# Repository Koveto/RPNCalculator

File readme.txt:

Reverse Polish Notation (RPN) Calculator

Contributors:
Kale Erickson
Kobe Goodwin
Gabe Wichmann

NDSU Senior Design project
ECE 403/405
Fall 2024 - Spring 2025
OneNote: https://ndusbpos-my.sharepoint.com/:o:/g/personal/kale_erickson_ndus_edu/EvFGwJnf-eBBiN7WtRWUvscBkYgOqBa3zW2gMm88qsdTBQ?e=oOiAU5

Project Description

HP-42S is a reverse polish notation (RPN) calculator championed by 
engineers around the world. RPN calculators sell for $400 and higher:
a forbidding price for college students. Our committee will design an
alternative HP-42S calculator that is affordable and reliable. Our 
RPN calculator solution will operate on mobile hardware powered by a
battery and disconnected from external devices. Our committee aims to
construct a RPN calculator engineering students could feasibly use on
exams. 

Instructions

1. Hold the button on the Raspberry Pi Pico
2. Plug the Pico into the computer
3. Drag "rp2-pico-micropython-doubleprecision-1-19.uf2" into the new directory
4. Unplug the Pico
5. Release the button
6. Plug the Pico into the computer
7. Use Thonny to save files in "program" to Pico

About the LCD

The program includes lcd.py and lcd_i2c.py.
lcd.py:
   communicates to the 20x4 LCD (using parallel interface)
lcd_i2c.py:
   NOT NECESSARY TO DOWNLOAD.
   used by an old PCB revision to communicate to its 16x2 LCD
   (using I2C protocol). 
To switch from one to the other,
   remove commented-out LCD_I2C import/initialization in main.py.
   comment out LCD import/initialization in main.py. 
Different LCD?
   the program only supports 20x4 parallel or 16x2 I2C.
   change ROWS and COLUMNS in lcd.py or lcd_i2c.py.
   revise lcd.write_to(...) commands in main.py and calculator.py.

Program your own game!

lcd.py is necessary.
Revise button_labels.py with your buttons and mapping.
Revise push_buttons.py if necessary.
Create your own main.py to read input and display output.

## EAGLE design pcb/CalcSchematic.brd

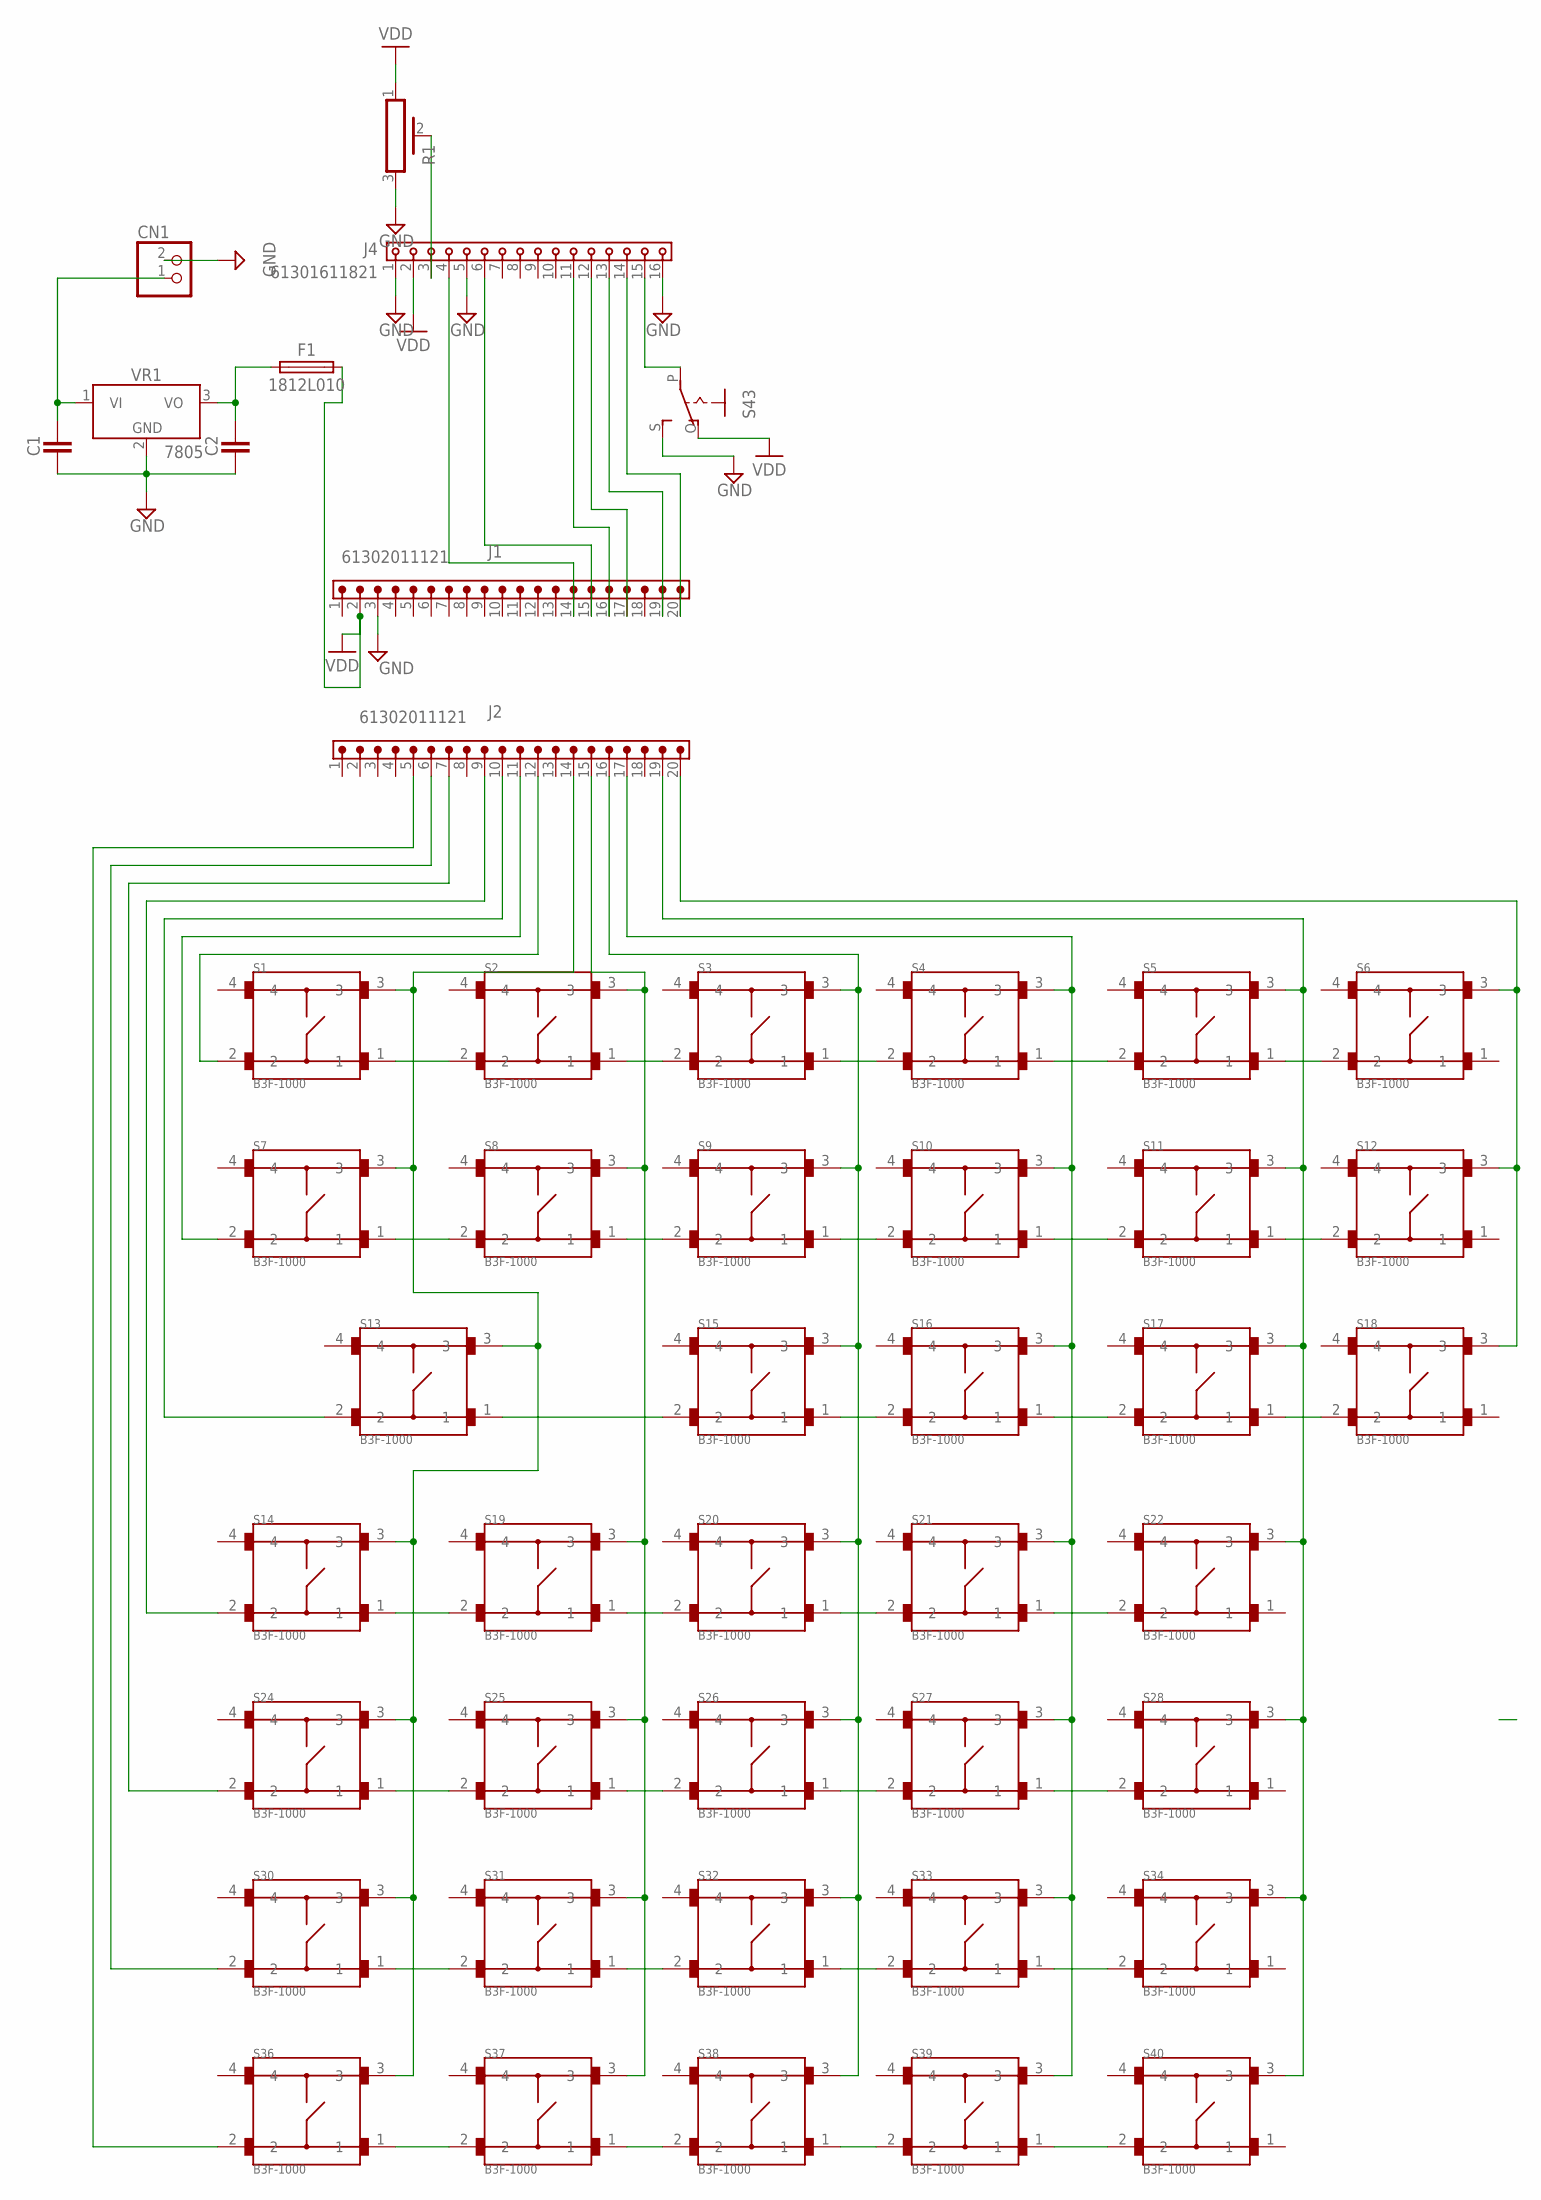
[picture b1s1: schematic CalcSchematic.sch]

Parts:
C1, C2: CAPACITOR_CHIP-1206(3216-METRIC); CAPC3216X135
CN1: JST_2PIN-THM; JST-PH-2-THM
F1: 1812L010; FUSC4532X125
J1, J2: 61302011121
J4: 61301611821
R1: POT_PV36P; PV36P
S1, S2, S3, S4, S5, S6, S7, S8, S9, S10, S11, S12, S13, S14, S15, S16, S17, S18, S19, S20, S21, S22, S24, S25, S26, S27, S28, S30, S31, S32, S33, S34, S36, S37, S38, S39, S40: B3F-1000; SW_B3F-1000
S43: EG1218S; EG1218
VR1: 7805; TO220V

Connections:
GND: C1.2, C2.2, CN1.2 (1), J1.3, J4.1, J4.5, J4.16, R1.3, S43.S, VR1.2 (GND)
unnamed: S1.1, S2.2
unnamed: S2.1, S3.2
unnamed: S3.1, S4.2
unnamed: S4.1, S5.2
unnamed: S5.1, S6.2
unnamed: S7.1, S8.2
unnamed: S8.1, S9.2
unnamed: S9.1, S10.2
unnamed: S10.1, S11.2
unnamed: S11.1, S12.2
unnamed: S13.1, S15.2
unnamed: S15.1, S16.2
unnamed: S16.1, S17.2
unnamed: S17.1, S18.2
unnamed: S14.1, S19.2
unnamed: S19.1, S20.2
unnamed: S20.1, S21.2
unnamed: S21.1, S22.2
unnamed: S24.1, S25.2
unnamed: S25.1, S26.2
unnamed: S26.1, S27.2
unnamed: S27.1, S28.2
unnamed: C2.1, F1.1, VR1.3 (VO)
unnamed: S30.1, S31.2
unnamed: S31.1, S32.2
unnamed: S32.1, S33.2
unnamed: S33.1, S34.2
unnamed: S36.1, S37.2
unnamed: S37.1, S38.2
unnamed: S38.1, S39.2
unnamed: S39.1, S40.2
unnamed: J2.14, S1.3, S7.3, S13.3, S14.3, S24.3, S30.3, S36.3
unnamed: J2.15, S2.3, S8.3, S19.3, S25.3, S31.3, S37.3
unnamed: J2.16, S3.3, S9.3, S15.3, S20.3, S26.3, S32.3, S38.3
unnamed: J2.17, S4.3, S10.3, S16.3, S21.3, S27.3, S33.3, S39.3
unnamed: J2.19, S5.3, S11.3, S17.3, S22.3, S28.3, S34.3, S40.3
unnamed: J2.20, S6.3, S12.3, S18.3
unnamed: J2.12, S1.2
unnamed: J2.11, S7.2
unnamed: J2.10, S13.2
unnamed: J2.9, S14.2
unnamed: J2.7, S24.2
unnamed: J2.6, S30.2
unnamed: J2.5, S36.2
unnamed: J4.3, R1.2
unnamed: J1.14, J4.4
unnamed: J1.15, J4.6
unnamed: J1.16, J4.11
unnamed: J1.17, J4.12
unnamed: J1.19, J4.13
unnamed: J1.20, J4.14
unnamed: J4.15, S43.P
unnamed: C1.1, CN1.1 (2), VR1.1 (VI)
VDD: F1.2, J1.2, J4.2, R1.1, S43.O

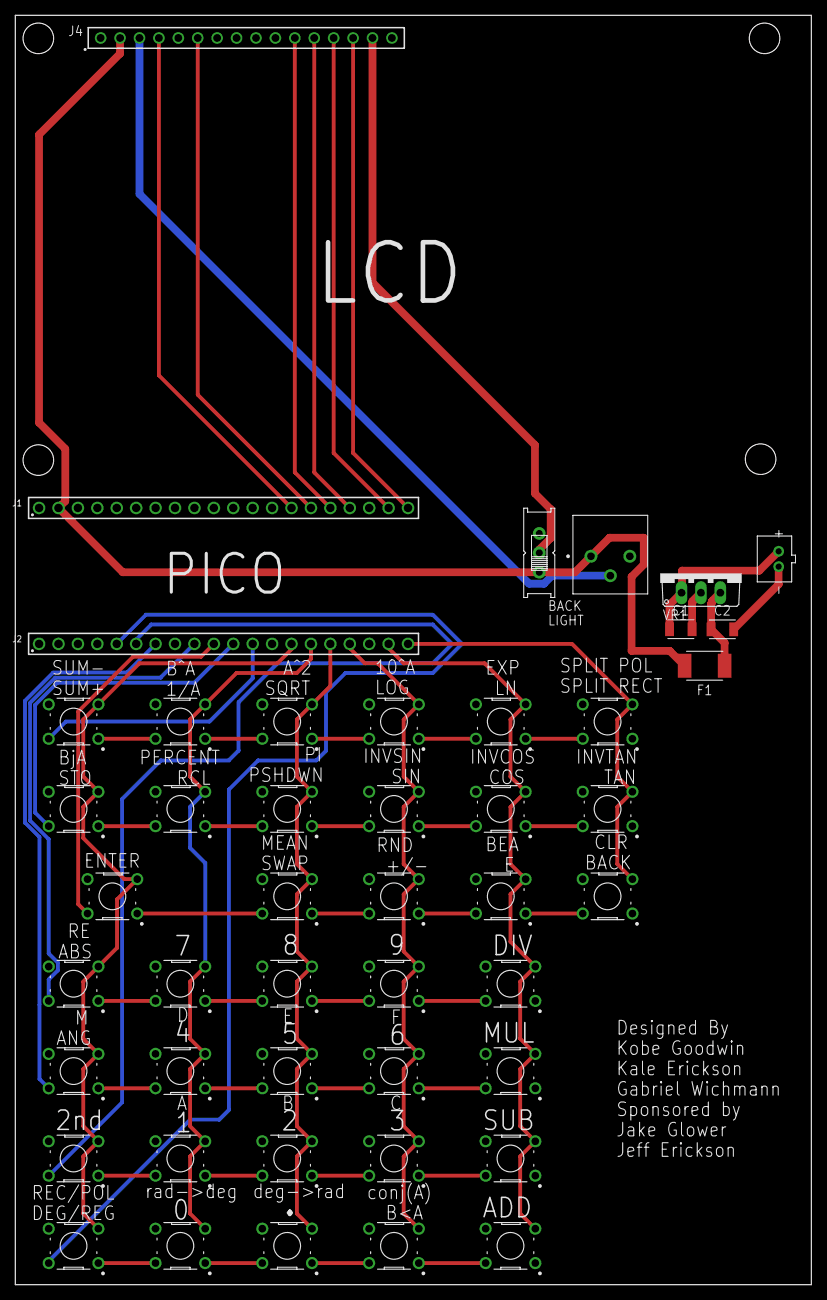
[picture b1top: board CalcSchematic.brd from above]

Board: 2 copper layers, 104.1 x 166.0 mm, 47 parts (0 on the bottom side), 55 nets.

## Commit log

2024-09-15 UI Button detection
2024-09-17 Numerical Input
2024-10-06 Arithmetic operations implemented. Divide By Zero displayed on top column when raised.
2024-10-06 Backspace/Enter methods resolved for numbers extending beyond DIGITS_ON_SCREEN
2024-10-06 Orange/Clear button
2024-10-06 Orange deactivates after use
2024-10-06 Fixed previous commit
2024-10-06 Division operands flipped
2024-10-06 Documented code. Simplified using peek() call.
2024-10-06 pushOperation flowchart
2024-10-06 appendZeros flowchart
2024-10-06 addition flowchart
2024-10-06 button35 flowchart
2024-10-06 button27 flowchart
2024-10-06 button22 flowchart
2024-10-06 button17 flowchart
2024-10-08 numberPressed flowchart
2024-10-08 Combined flowcharts pdf
2024-10-28 Pico button detection
2024-10-29 Keypad input detection
2024-10-29 Keypad + Button input
2024-10-29 Task 1 Functions to Pico
2024-10-29 Fourth button: Orange/Clear
2024-11-12 Decimal input
2024-11-12 One digit exponentiation
2024-11-12 Input "complex" numbers
2024-12-15 Push button inverter
2024-12-16 Complex/Exponential arithmetic
2024-12-20 connectLCD
2024-12-20 Button Array
2024-12-21 rpnCalculator I/O
2024-12-22 Addition/Subtraction
2024-12-23 Long Division
2024-12-24 Multiplication/Division
2024-12-27 Stack
2025-01-01 Real Whole Number Input
2025-02-11 I2C Connection
2025-02-11 Documented code and removed old breadboard programs
2025-02-11 Emptied display, removed old imports
2025-02-11 Progress on single precision solution
2025-02-13 Program revision
2025-02-13 Trig, Log, Negate, Reciprocal, Swap
2025-02-13 Morning's code
2025-02-14 Complex revisions in progress
2025-02-16 Main flowchart
2025-02-17 Push Button Flowchart
2025-02-24 Squish complex numbers
2025-03-03 Button Labels added
2025-03-03 Button Labels
2025-03-03 Parallel program drafted
2025-03-19 Four row display
2025-04-14 Free42 Sim
2025-04-23 Added modulus and gamma
2025-04-25 Started on adding hex
2025-04-28 Fixed orient bug. Add hex support
2025-05-04 Two minute video
2025-05-04 Cleaned up repo
2025-05-07 Condensed parallel LCD functions to lcd.py. Integrated old I2C code so program can run on old PCB
2025-05-08 Simplified deprecated I2C functions into lcd_i2c.py. Program now works for both old and new PCB
2025-05-08 Button functions pdf
2025-05-08 Commented out LCD_I2C lines. Added info to readme and poster pdf
2025-05-12 pcb files

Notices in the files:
parts and their libraries:
Wurth_Connectors_WR-PHD: Copyright: Würth Elektronik
